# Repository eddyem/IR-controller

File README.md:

IR-controller
=============

Clone of same project from sourceforge

Don't use files from root directory, they are obsolete!!! 
Current code is in directory with_opencm3.

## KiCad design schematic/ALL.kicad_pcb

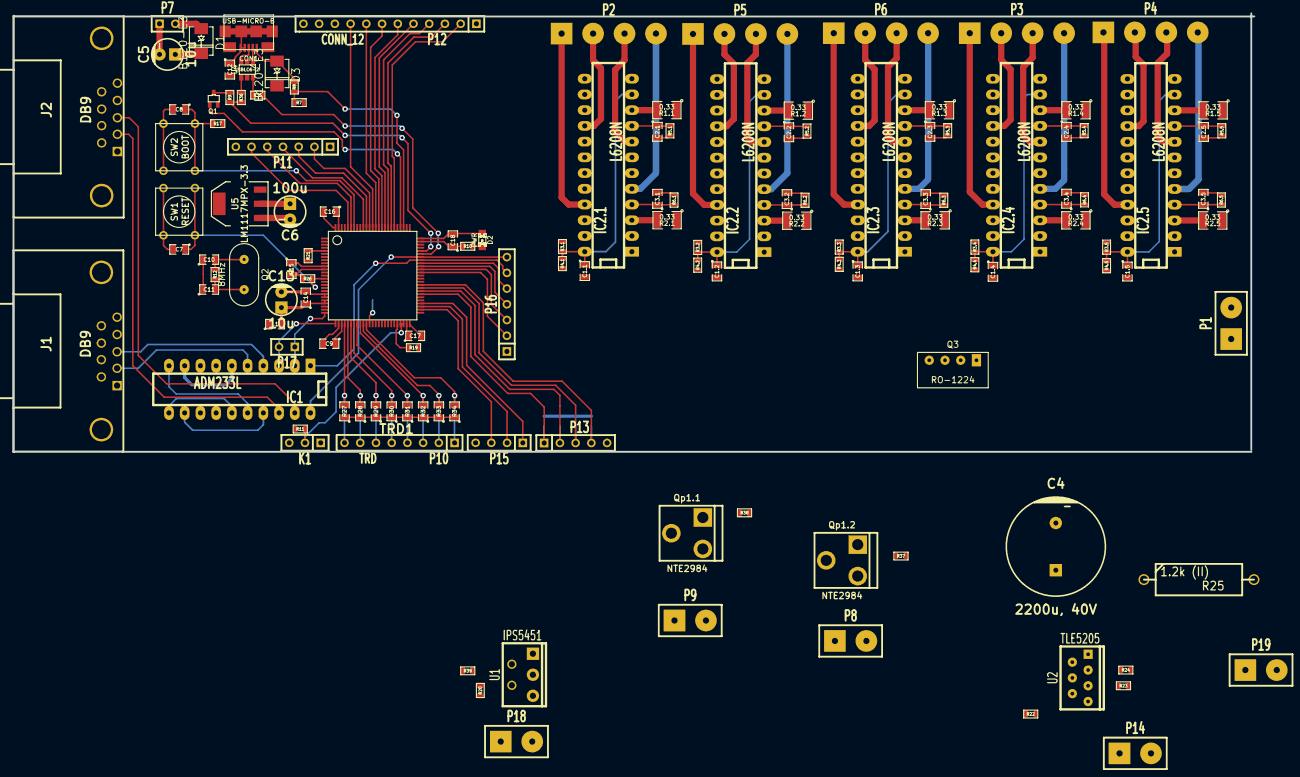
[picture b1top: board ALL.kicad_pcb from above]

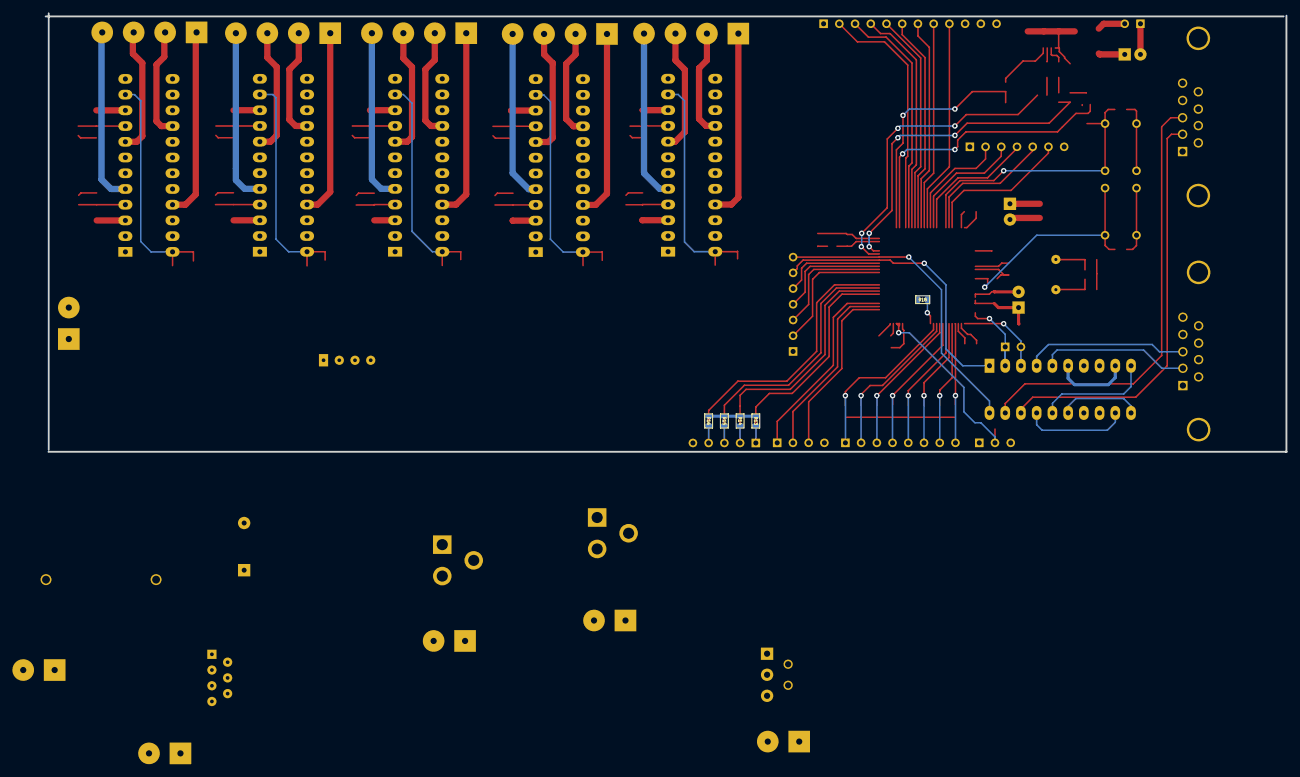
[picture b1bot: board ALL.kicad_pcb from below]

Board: 4 copper layers, 200.5 x 70.9 mm, 138 parts (5 on the bottom side), 142 nets.

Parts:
C1.1, C1.2, C1.3, C1.4, C1.5: 68n; SM0805
C2.1, C2.2, C2.3, C2.4, C2.5, C3.1, C3.2, C3.3, C3.4, C3.5: 1n; SM0805
C4: 2200u, 40V; CP_16x25mm
C5, C13: 10u; CP_5x11mm
C6: 100u; CP_5x11mm
C7, C8, C9, C12, C14, C15, C16, C17, C18: 100n; SM0805
C10, C11: 27p; SM0805
CON1: USB-MICRO-B; MICRO-B-USB
D1, D3: B120-E3; DO214
D2: PWR; LED-0805
IC1: ADM233L; DIP-20__300_ELL
IC2.1, IC2.2, IC2.3, IC2.4, IC2.5: L6208N; DIP-24__300_ELL
J1, J2: DB9; DB9FC
K1: CONN_3; SIL-3
L1: BMB2A0300AN1; SM0805
P1, P8, P9, P14, P18, P19: CONN_2; SIL-2-power
P2, P3, P4, P5, P6: CONN_4; SIL-4-power
P7, P17: CONN_2; SIL-2
P10: TRD; SIL-8
P11, P16: CONN_7; SIL-7
P12: CONN_12; SIL-12
P13: CONN_5; SIL-5
P15: CONN_4; SIL-4
Q1: DTA114Y; SOT323
Q2: 8MHz; hc49
Q3: RO-1224; SIP-4-RO
Qp1.1, Qp1.2: NTE2984; TO220-3-vert
R1.1, R1.2, R1.3, R1.4, R1.5, R2.1, R2.2, R2.3, R2.4, R2.5: 0.33; SM1210
R3.1, R3.2, R3.3, R3.4, R3.5, R7: 22k; SM0603
R4.1, R4.2, R4.3, R4.4, R4.5: 1.8k; SM0603
R5.1, R5.2, R5.3, R5.4, R5.5, R6.1, R6.2, R6.3, R6.4, R6.5: 51k; SM0603
R8, R20, R21: 15k; SM0603
R9: 1.5k; SM0603
R10: 510; SM0603
R11, R19: 4.7k; SM0603
R12: 1M; SM0603
R13, R14, R15, R16, R17, R22, R23, R24, R26, R37, R38, R39: 10k; SM0603
R18: 100k; SM0603
R25: 1.2k (II); R7
R27, R28, R29, R30, R31, R32, R33, R34: RT0805BRB071KL; SM0805
R35, R36: 22; SM0603
SW1: RESET; SW_PUSH_SMALL
SW2: BOOT; SW_PUSH_SMALL
U1: IPS5451; TO220-5
U2: TLE5205; TO220-7-12
U3: STM32F103; LQFP100_STM32
U4: USBLC6-2; SOT23_6
U5: LM1117MPX-3.3; SOT-223

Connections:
+3.3V: C6.1, C8.2, C9.1, C12.2, C15.2, C16.2, C17.2, C18.2, D2.1, L1.1, P11.7, Q1.2, R11.2, R20.2, R22.1, R23.1, R24.1, R26.2, SW2.1, U3.11, U3.28, U3.50, U3.75, U3.100, U4.5, U5.2
+5V: C5.1, D1.2, D3.2, IC1.7, IC2.1.13, IC2.1.23, IC2.2.13, IC2.2.23, IC2.3.13, IC2.3.23, IC2.4.13, IC2.4.23, IC2.5.13, IC2.5.23, K1.3, P12.1, R3.1.2, R3.2.2, R3.3.2, R3.4.2, R3.5.2, R13.2, R14.2, R15.2, R16.2, U5.3
/EP0: P13.1, R13.1, U3.57
/EP1: P13.2, R14.1, U3.58
/EP2: P13.3, R15.1, U3.59
/EP3: P13.4, R16.1, U3.60
/Filters slit #1/+10V: IC2.1.17, IC2.1.20, IC2.2.17, IC2.2.20, IC2.3.17, IC2.3.20, IC2.4.17, IC2.4.20, IC2.5.17, IC2.5.20, P1.2, P8.2, P9.2, Q3.1, U1.3
/Filters slit #1/+24V: IC2.1.15, IC2.2.15, IC2.3.15, IC2.4.15, IC2.5.15, Q3.3
/Filters slit #1/A: IC2.2.21, P5.1
/Filters slit #1/A*: IC2.2.16, P5.2
/Filters slit #1/B: IC2.2.5, P5.4
/Filters slit #1/B*: IC2.2.8, P5.3
/Filters slit #1/SM_CLK: IC2.1.1, IC2.2.1, IC2.3.1, U3.63
/Filters slit #1/SM_DIR: IC2.2.2, U3.98
/Filters slit #1/SM_EN: IC2.2.14, U3.39
/Filters slit #2/A: IC2.3.21, P6.1
/Filters slit #2/A*: IC2.3.16, P6.2
/Filters slit #2/B: IC2.3.5, P6.4
/Filters slit #2/B*: IC2.3.8, P6.3
/Filters slit #2/SM_DIR: IC2.3.2, U3.1
/Filters slit #2/SM_EN: IC2.3.14, U3.40
/Hall0: P12.2, U3.81
/Hall1: P12.3, U3.82
/Hall2: P12.4, U3.83
/Hall3: P12.5, U3.84
/Hall4: P12.6, U3.85
/Hall5: P12.7, U3.86
/Hall6: P12.8, U3.87
/Hall7: P12.9, U3.88
/Hall8: P12.10, U3.55
/Hall9: P12.11, U3.56
/Long stage/A: IC2.4.21, P3.1
/Long stage/A*: IC2.4.16, P3.2
/Long stage/B: IC2.4.5, P3.4
/Long stage/B*: IC2.4.8, P3.3
/Long stage/SM_CLK: IC2.4.1, IC2.5.1, U3.24
/Long stage/SM_DIR: IC2.4.2, U3.2
/Long stage/SM_EN: IC2.4.14, U3.41
/POW3: R19.2, R39.1, U3.46
/Power MOSFET module 1/GND_OUT: P8.1, Qp1.2.2
/Power MOSFET module 1/ON: Qp1.2.1, R37.1, U3.44
/Power MOSFET module 2/GND_OUT: P9.1, Qp1.1.2
/Power MOSFET module 2/ON: Qp1.1.1, R38.1, U3.45
/STM32F103 module/1-WIRE: K1.2, R11.1, U3.47, U3.48
/STM32F103 module/BOOT: C8.1, R17.1, SW2.2, U3.94
/STM32F103 module/DG_FEEDBACK: R21.1, U3.5
/STM32F103 module/EXT0: P16.2, U3.64
/STM32F103 module/EXT1: P16.3, U3.65
/STM32F103 module/EXT2: P16.4, U3.66
/STM32F103 module/EXT3: P16.5, U3.67
/STM32F103 module/I2C_SCL/CANRX: P11.5, U3.95
/STM32F103 module/I2C_SDA/CANTX: P11.6, U3.96
/STM32F103 module/RS-232 level converter/UART_RX: IC1.3, P17.2, U3.26
/STM32F103 module/RS-232 level converter/UART_RX1: IC1.20, P16.7, U3.69
/STM32F103 module/RS-232 level converter/UART_TX: IC1.2, P17.1, U3.25
/STM32F103 module/RS-232 level converter/UART_TX1: IC1.1, P16.6, U3.68
/STM32F103 module/RST: C7.1, R26.1, SW1.2, U3.14
/STM32F103 module/SHTR_FEEDBACK: R20.1, R21.2, U1.4
/STM32F103 module/SPI1_MISO: P11.3, U3.90
/STM32F103 module/SPI1_MOSI: P11.4, U3.91
/STM32F103 module/SPI1_SCK: P11.2, U3.89
/STM32F103 module/SPI2_MISO: P15.2, U3.53
/STM32F103 module/SPI2_MOSI: P15.1, U3.54
/STM32F103 module/SPI2_SCK: P15.3, U3.52
/STM32F103 module/USB input circuit/USB_DISC: Q1.1, U3.79
/STM32F103 module/USB input circuit/USB_DM: R35.2, U3.70
/STM32F103 module/USB input circuit/USB_DP: R9.2, R36.2, U3.71
/STM32F103 module/USB input circuit/USB_POWER: R7.1, R8.1, U3.78
/STM32F103 module/VDDA: C13.1, C14.1, L1.2, R27.1, R28.1, R29.1, R30.1, R31.1, R32.1, R33.1, R34.1, U3.21, U3.22
/Short stage/A: IC2.5.21, P4.1
/Short stage/A*: IC2.5.16, P4.2
/Short stage/B: IC2.5.5, P4.4
/Short stage/B*: IC2.5.8, P4.3
/Short stage/SM_DIR: IC2.5.2, U3.3
/Short stage/SM_EN: IC2.5.14, U3.42
/Shutter MOSFET/+36V: P19.2, R25.1
/Shutter MOSFET/EF: R22.2, U2.2, U3.16
/Shutter MOSFET/IN1: R24.2, U2.3, U3.43
/Shutter MOSFET/IN2: R23.2, U2.5, U3.15
/Shutter MOSFET/OUT1: P14.2, U2.1
/Shutter MOSFET/OUT2: P14.1, U2.7
/T1_0: P10.1, R34.2, U3.36
/T1_1: P10.2, R33.2, U3.35
/T1_2: P10.3, R32.2, U3.34
/T1_3: P10.4, R31.2, U3.33
/T1_4: P10.5, R30.2, U3.32
/T1_5: P10.6, R29.2, U3.31
/T1_6: P10.7, R28.2, U3.30
/T1_7: P10.8, R27.2, U3.29
/Turret slits/A: IC2.1.21, P2.1
/Turret slits/A*: IC2.1.16, P2.2
/Turret slits/B: IC2.1.5, P2.4
/Turret slits/B*: IC2.1.8, P2.3
/Turret slits/SM_DIR: IC2.1.2, U3.97
/Turret slits/SM_EN: IC2.1.14, U3.38
GND: C1.1.2, C1.2.2, C1.3.2, C1.4.2, C1.5.2, C2.1.2, C2.2.2, C2.3.2, C2.4.2, C2.5.2, C3.1.2, C3.2.2, C3.3.2, C3.4.2, C3.5.2, C4.2, C5.2, C6.2, C7.2, C9.2, C10.1, C11.1, C12.1, C13.2, C14.2, C15.1, C16.1, C17.1, C18.1, CON1.4, CON1.5, CON1.6, CON1.7, CON1.8, CON1.9, IC1.6, IC1.9, IC2.1.6, IC2.1.7, IC2.1.12, IC2.1.18, IC2.1.19, IC2.2.6, IC2.2.7, IC2.2.12, IC2.2.18, IC2.2.19, IC2.3.6, IC2.3.7, IC2.3.12, IC2.3.18, IC2.3.19, IC2.4.6, IC2.4.7, IC2.4.12, IC2.4.18, IC2.4.19, IC2.5.6, IC2.5.7, IC2.5.12, IC2.5.18, IC2.5.19, J1.5, J2.5, K1.1, P1.1, P7.1, P11.1, P12.12, P13.5, P15.4, P16.1, P18.1, P19.1, Q3.2, Q3.4, Qp1.1.3, Qp1.2.3, R1.1.1, R1.2.1, R1.3.1, R1.4.1, R1.5.1, R2.1.1, R2.2.1, R2.3.1, R2.4.1, R2.5.1, R4.1.2, R4.2.2, R4.3.2, R4.4.2, R4.5.2, R5.1.2, R5.2.2, R5.3.2, R5.4.2, R5.5.2, R6.1.2, R6.2.2, R6.3.2, R6.4.2, R6.5.2, R7.2, R10.1, R17.2, R18.2, R37.2, R38.2, R39.2, SW1.1, U1.1, U2.4, U3.10, U3.19, U3.20, U3.27, U3.49, U3.74, U3.99, U4.2, U5.1
unnamed: R19.1, U1.2
unnamed: P18.2, U1.5
unnamed: D1.1, P7.2
unnamed: C3.3.1, IC2.3.4, R6.3.1
unnamed: C2.3.1, IC2.3.9, R5.3.1
unnamed: IC2.3.3, R2.3.2
unnamed: IC2.3.10, R1.3.2
unnamed: C1.3.1, IC2.3.11, IC2.3.24, R3.3.1, R4.3.1
unnamed: R18.1, U3.37
unnamed: D2.2, R10.2
unnamed: C10.2, Q2.2, R12.1, U3.12
unnamed: C11.2, Q2.1, R12.2, U3.13
unnamed: C3.2.1, IC2.2.4, R6.2.1
unnamed: C2.2.1, IC2.2.9, R5.2.1
unnamed: IC2.2.3, R2.2.2
unnamed: IC2.2.10, R1.2.2
unnamed: C1.2.1, IC2.2.11, IC2.2.24, R3.2.1, R4.2.1
unnamed: C2.1.1, IC2.1.9, R5.1.1
unnamed: C1.1.1, IC2.1.11, IC2.1.24, R3.1.1, R4.1.1
unnamed: IC2.1.10, R1.1.2
unnamed: C3.1.1, IC2.1.4, R6.1.1
unnamed: IC2.1.3, R2.1.2
unnamed: IC2.5.10, R1.5.2
unnamed: C1.5.1, IC2.5.11, IC2.5.24, R3.5.1, R4.5.1
unnamed: C2.5.1, IC2.5.9, R5.5.1
unnamed: C3.5.1, IC2.5.4, R6.5.1
unnamed: IC2.5.3, R2.5.2
unnamed: IC2.4.3, R2.4.2
unnamed: IC2.4.10, R1.4.2
unnamed: C2.4.1, IC2.4.9, R5.4.1
unnamed: C3.4.1, IC2.4.4, R6.4.1
unnamed: C1.4.1, IC2.4.11, IC2.4.24, R3.4.1, R4.4.1
unnamed: C4.1, R25.2, U2.6
unnamed: IC1.5, J1.2
unnamed: IC1.4, J1.3
unnamed: IC1.12, IC1.17
unnamed: IC1.11, IC1.15
unnamed: IC1.10, IC1.16
unnamed: IC1.18, J2.2
unnamed: IC1.19, J2.3
unnamed: Q1.3, R9.1
unnamed: R36.1, U4.4
unnamed: R35.1, U4.6
unnamed: CON1.2, U4.1
unnamed: CON1.3, U4.3
unnamed: CON1.1, D3.1, R8.2

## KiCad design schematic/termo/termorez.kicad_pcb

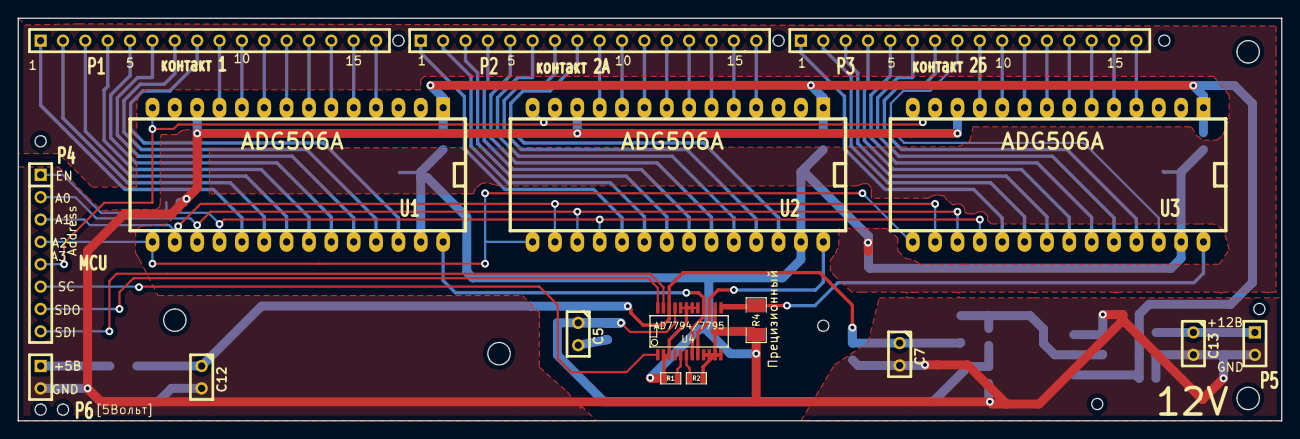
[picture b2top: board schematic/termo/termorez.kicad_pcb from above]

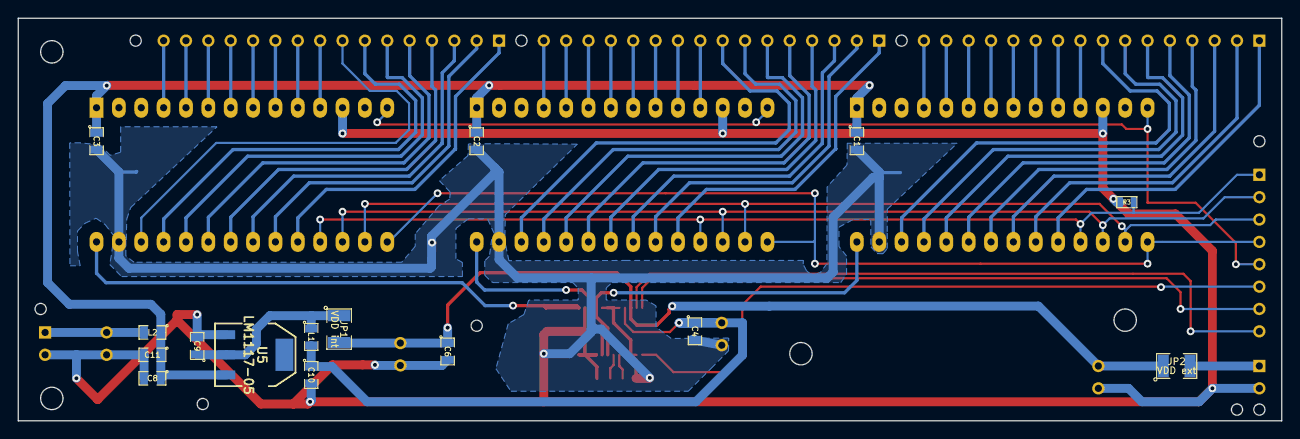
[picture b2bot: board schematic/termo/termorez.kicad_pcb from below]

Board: 2 copper layers, 143.5 x 45.7 mm, 32 parts (15 on the bottom side), 68 nets.

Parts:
C1, C2, C3, C4, C6, C9: 0.1u; SM0805
C5, C7, C12: 10u; C1
C8: 0.33u; SM0805
C10, C11: 1u; SM0805
C13: 100u; C1
JP1: VDD int; SM1210
JP2: VDD ext; SM1210
L1, L2: BMB2A0300AN1; SM0805
P1: контакт 1; SIL-16
P2: контакт 2А; SIL-16
P3: контакт 2Б; SIL-16
P4: MCU; SIL-8
P5: 12V; SIL-2
P6: 5Вольт; SIL-2
R1, R2: 10k; SM0603
R3: 47k; SM0603
R4: 5.1k PREC!; SM1206
U1, U2, U3: ADG506A; DIP-28__600_ELL
U4: AD7794/7795; SSOP24
U5: LM1117-05; SOT223

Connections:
+5VA: C4.1, C5.1, C10.1, L1.2, U4.21
+12V: C1.1, C2.1, C3.1, C8.1, C11.1, L2.1, U1.1, U2.1, U3.1, U5.3
+12Vex: C13.1, L2.2, P5.1
/A0: P4.2, U1.17, U2.17, U3.17
/A1: P4.3, U1.16, U2.16, U3.16
/A2: P4.4, U1.15, U2.15, U3.15
/A3: P4.5, U1.14, U2.14, U3.14
/EN: P4.1, R3.1, U1.18, U2.18, U3.18
/SC: P4.6, U4.1
/SDI: P4.8, U4.23
/SDO: P4.7, U4.24
DVDD: JP2.2, P6.1
GND: C1.2, C2.2, C3.2, C4.2, C5.2, C6.2, C7.2, C8.2, C9.2, C10.2, C11.2, C12.2, C13.2, P5.2, P6.2, R1.2, R2.2, R3.2, R4.2, U1.12, U1.27, U2.12, U2.27, U3.12, U3.27, U4.2, U4.3, U4.9, U4.10, U4.11, U4.12, U4.14, U4.17, U4.18, U4.19, U4.20, U5.1
unnamed: P1.3, U1.21
unnamed: P1.2, U1.20
unnamed: P1.1, U1.19
unnamed: P1.16, U1.4
unnamed: P1.15, U1.5
unnamed: P1.14, U1.6
unnamed: P1.13, U1.7
unnamed: P1.12, U1.8
unnamed: P1.11, U1.9
unnamed: P1.10, U1.10
unnamed: P1.9, U1.11
unnamed: P1.8, U1.26
unnamed: P1.7, U1.25
unnamed: P1.6, U1.24
unnamed: P1.5, U1.23
unnamed: P1.4, U1.22
unnamed: R2.1, U4.6
unnamed: P2.3, U2.21
unnamed: P2.2, U2.20
unnamed: P2.1, U2.19
unnamed: P2.16, U2.4
unnamed: P2.15, U2.5
unnamed: P2.14, U2.6
unnamed: P2.13, U2.7
unnamed: P2.12, U2.8
unnamed: P2.11, U2.9
unnamed: P2.10, U2.10
unnamed: P2.9, U2.11
unnamed: P2.8, U2.26
unnamed: P2.7, U2.25
unnamed: P2.6, U2.24
unnamed: P2.5, U2.23
unnamed: P2.4, U2.22
unnamed: R1.1, U4.5
unnamed: R4.1, U3.28, U4.13
unnamed: U1.28, U4.7, U4.16
unnamed: U2.28, U4.8, U4.15
unnamed: C9.1, JP1.1, L1.1, U5.2
unnamed: P3.3, U3.21
unnamed: P3.2, U3.20
unnamed: P3.1, U3.19
unnamed: P3.16, U3.4
unnamed: P3.15, U3.5
unnamed: P3.14, U3.6
unnamed: P3.13, U3.7
unnamed: P3.12, U3.8
unnamed: P3.11, U3.9
unnamed: P3.10, U3.10
unnamed: P3.9, U3.11
unnamed: P3.8, U3.26
unnamed: P3.7, U3.25
unnamed: P3.6, U3.24
unnamed: P3.5, U3.23
unnamed: P3.4, U3.22
VDD: C6.1, C7.1, C12.1, JP1.2, JP2.1, U4.22

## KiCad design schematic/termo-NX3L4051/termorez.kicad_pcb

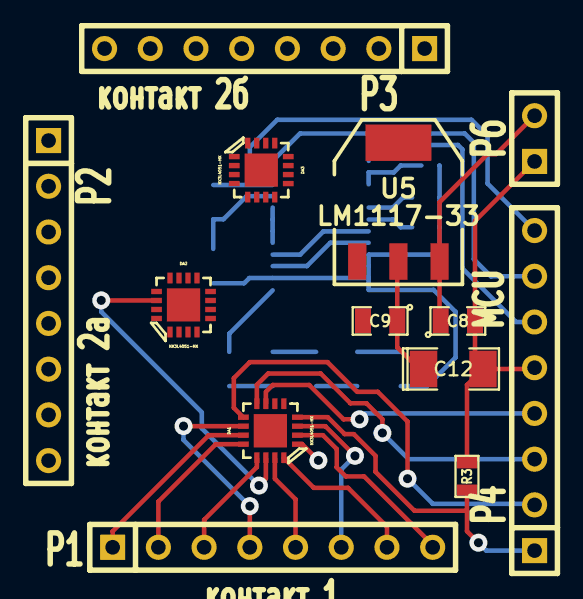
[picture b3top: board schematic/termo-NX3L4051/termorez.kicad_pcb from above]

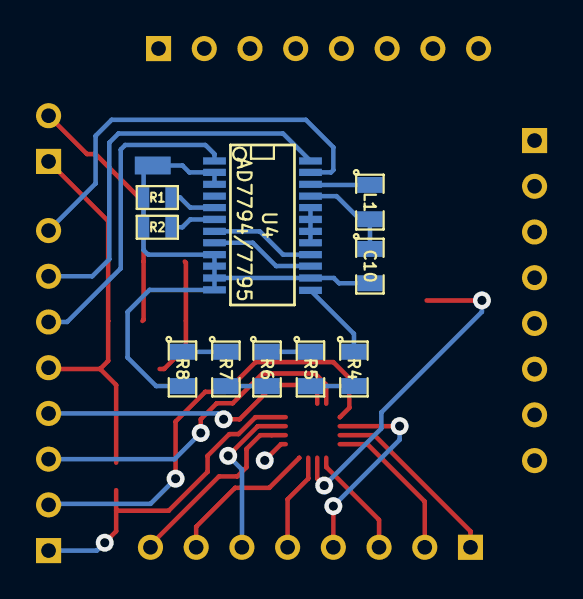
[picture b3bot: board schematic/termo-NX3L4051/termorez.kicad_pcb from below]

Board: 2 copper layers, 24 parts (11 on the bottom side), 45 nets.

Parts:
C8: 0.33u; SM0805
C9: 0.1u; SM0805
C10: 1u; SM0805
C12: 47u; SM1206POL
DA1, DA2, DA3: NX3L4051-HX; HXQFN16
L1: BMB2A0300AN1; SM0805
P1: контакт 1; SIL-8
P2: контакт 2a; SIL-8
P3: контакт 2б; SIL-8
P4: MCU; SIL-8
P6: 5V; SIL-2
R1, R2: 10k; SM0603
R3: 47k; SM0603
R4, R5, R6, R7, R8: 1k 0.1% (RT0805BRB071KL); SM0805
U4: AD7794/7795; SSOP24
U5: LM1117-33; SOT223
X1: GND_CONNECTOR; GND_connector

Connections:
+3.3V: C10.1, L1.2, U4.21
/A0: DA1.9, DA2.9, DA3.9, P4.2
/A1: DA1.8, DA2.8, DA3.8, P4.3
/A2: DA1.7, DA2.7, DA3.7, P4.4
/EN: DA1.4, DA2.4, DA3.4, P4.1, R3.1
/SC: P4.6, U4.1
/SDI: P4.8, U4.23
/SDO: P4.7, U4.24
AGND: C10.2, DA1.6, DA2.6, DA3.6, R1.2, R2.2, R8.2, U4.9, U4.10, U4.11, U4.12, U4.14, U4.17, U4.18, U4.19, U4.20, X1.2
DVDD: C8.1, P6.2, U5.3
GND: C8.2, C9.2, C12.2, P4.5, P6.1, R3.2, U4.2, U4.3, U5.1, X1.1
unnamed: DA1.1, U4.7, U4.16
unnamed: DA3.16, P3.7
unnamed: DA3.3, P3.6
unnamed: DA3.2, P3.8
unnamed: DA1.16, P1.7
unnamed: DA1.15, P1.5
unnamed: DA1.13, P1.3
unnamed: DA2.3, P2.6
unnamed: DA2.13, P2.3
unnamed: DA2.12, P2.2
unnamed: DA2.11, P2.1
unnamed: DA2.10, P2.4
unnamed: DA1.12, P1.2
unnamed: DA2.2, P2.8
unnamed: DA3.10, P3.4
unnamed: DA3.13, P3.3
unnamed: DA3.12, P3.2
unnamed: DA3.11, P3.1
unnamed: DA2.16, P2.7
unnamed: DA2.15, P2.5
unnamed: DA3.15, P3.5
unnamed: DA1.11, P1.1
unnamed: DA1.10, P1.4
unnamed: DA1.3, P1.6
unnamed: DA1.2, P1.8
unnamed: R4.2, R5.2
unnamed: R6.2, R7.2
unnamed: R5.1, R6.1
unnamed: R7.1, R8.1
unnamed: DA3.1, R4.1, U4.13
unnamed: DA2.1, U4.8, U4.15
unnamed: R2.1, U4.6
unnamed: R1.1, U4.5
VDD: C9.1, C12.1, DA1.14, DA2.14, DA3.14, L1.1, U4.22, U5.2

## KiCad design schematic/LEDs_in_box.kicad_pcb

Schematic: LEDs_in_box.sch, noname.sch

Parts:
D1, D2, D3, D4, D5: LED
HOLE1, HOLE2, HOLE3, HOLE4: HOLE
K1: CONN_3
K2: CONN_4
R1, R2: 330; SM0603
R3, R4: 2.2k; SM0603
R5: 6.8k; SM1206

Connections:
unnamed: D3.1 (A), K2.1
unnamed: D4.1 (A), K2.3
unnamed: D5.2 (K), R5.2
unnamed: K2.4, R3.1, R4.1, R5.1
unnamed: D4.2 (K), R4.2
unnamed: D3.2 (K), R3.2
unnamed: D5.1 (A), K2.2
unnamed: D1.1 (A), R1.2
unnamed: D1.2 (K), K1.1
unnamed: D2.2 (K), K1.2 (PM)
unnamed: K1.3, R1.1, R2.1
unnamed: D2.1 (A), R2.2

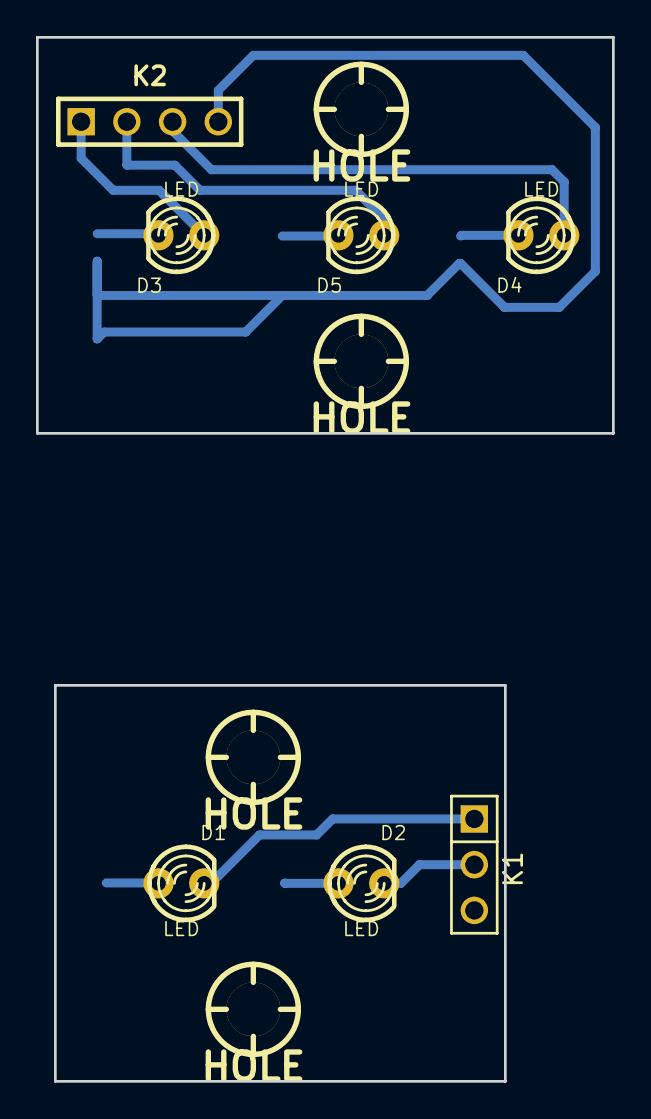
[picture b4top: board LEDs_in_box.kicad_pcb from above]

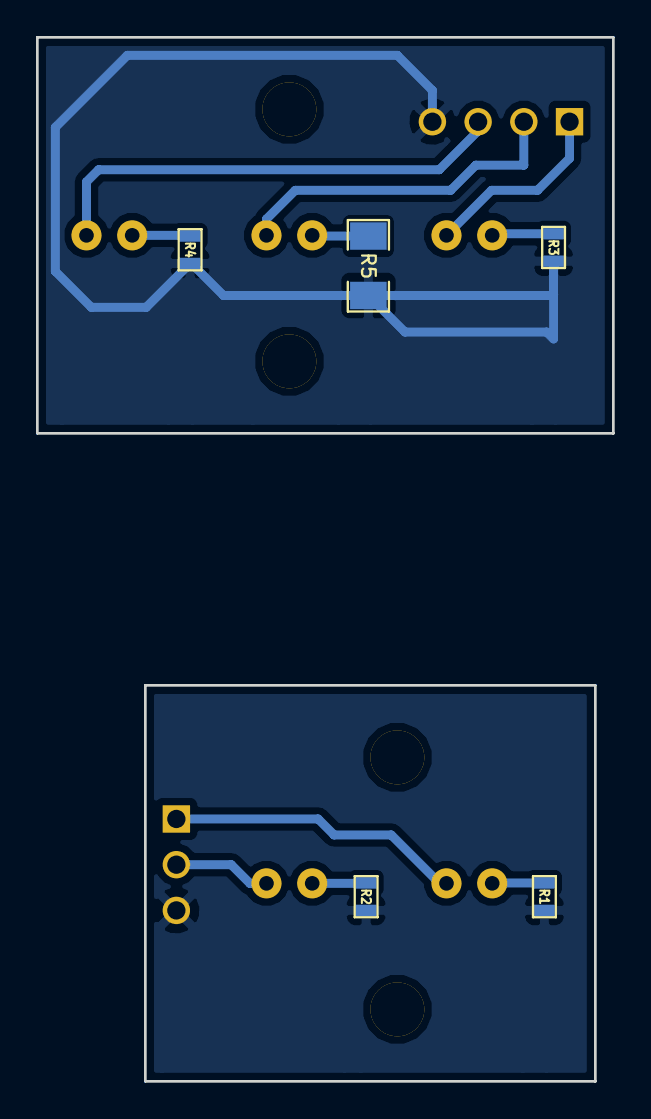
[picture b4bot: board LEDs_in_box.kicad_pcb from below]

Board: 2 copper layers, 32.0 x 58.0 mm, 16 parts (5 on the bottom side), 12 nets.

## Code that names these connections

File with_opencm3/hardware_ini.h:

/*
 * hardware_ini.h
 *
 * Copyright 2014 Edward V. Emelianov <eddy@sao.ru, edward.emelianoff@gmail.com>
 *
 * This program is free software; you can redistribute it and/or modify
 * it under the terms of the GNU General Public License as published by
 * the Free Software Foundation; either version 2 of the License, or
 * (at your option) any later version.
 *
 * This program is distributed in the hope that it will be useful,
 * but WITHOUT ANY WARRANTY; without even the implied warranty of
 * MERCHANTABILITY or FITNESS FOR A PARTICULAR PURPOSE.  See the
 * GNU General Public License for more details.
 *
 * You should have received a copy of the GNU General Public License
 * along with this program; if not, write to the Free Software
 * Foundation, Inc., 51 Franklin Street, Fifth Floor, Boston,
 * MA 02110-1301, USA.
 */

#pragma once
#ifndef __HARDWARE_INI_H__
#define __HARDWARE_INI_H__


// to have a compatibility with medium-density devices we can use only timers 1..4!!!
/*
 * Timers:
 * SysTick - system time
 * TIM1 - not used
 * TIM2 - 1-wire
 * TIM3, TIM4 - stepper motors
 */


extern volatile uint16_t ADC_value[]; // ADC DMA value

#define TRD_NO			(8) // number of TRD devices
// bits used to address external SPI ADC - PD10..12
#define ADC_ADDR_MASK	(GPIO10|GPIO11|GPIO12)
#define ADC_SET_ADDR(X)	((X << 10) & ADC_ADDR_MASK)
#define ADC_EN_PIN		GPIO13
#define ADC_ADDR_PORT	GPIOD

void SPI1_init();
void SPI2_init();
void GPIO_init();
void SysTick_init();
void ADC_init();
void ADC_calibrate_and_start();

void adc_dma_on();

/*
 * USB interface
 */
// USB_DICS (disconnect) - PC11
#define USB_DISC_PIN		GPIO11
#define USB_DISC_PORT		GPIOC
// USB_POWER (high level when USB connected to PC)
#define USB_POWER_PIN		GPIO10
#define USB_POWER_PORT		GPIOC
// change signal level on USB diconnect pin
#define usb_disc_high()   gpio_set(USB_DISC_PORT, USB_DISC_PIN)
#define usb_disc_low()    gpio_clear(USB_DISC_PORT, USB_DISC_PIN)
// in case of n-channel FET on 1.5k pull-up change on/off disconnect means low level
// in case of pnp bipolar transistor or p-channel FET on 1.5k pull-up disconnect means high level
#define usb_disconnect()  usb_disc_high()
#define usb_connect()     usb_disc_low()

/*
 * Stepper motors
 * motors' interface use timers 1 & 2, so even hardware-dependent functions are
 * 		moved to stepper_motors.c
 */
// PE7..11 - EN
#define MOTOR_EN_MASK		(0x1f << 7)
#define MOTOR_EN_PORT		(GPIOE)
// N == 0..4
#define MOTOR_EN_PIN(N)		(GPIO7 << (N))
// PE0..PE5 - DIR
#define MOTOR_DIR_MASK		(0x1f)
#define MOTOR_DIR_PORT		(GPIOE)
// N == 0..4
#define MOTOR_DIR_PIN(N)	(GPIO0 << (N))
// timers: TIM1 - PC6, TIM2 - PD15
#define MOTOR_TIM1_PORT		(GPIOC)
#define MOTOR_TIM1_PIN		(GPIO6)
#define MOTOR_TIM2_PORT		(GPIOD)
#define MOTOR_TIM2_PIN		(GPIO15)
// don't even try to move motor if motors' voltage less than 9.0V
#define MOTORS_VOLTAGE_THRES  (900)
// stop all motors if voltage less than 7.5V
#define MOTORS_VOLTAGE_ALERT  (750)

/*
 * One Wire interface
 *
// In case of using other USART for 1-wire port, make corresponding change
// and redefine pins in OW_Init
#define OW_USART_X			USART2
#define OW_RX_PORT			GPIO_BANK_USART2_RX
#define OW_RX_PIN			GPIO_USART2_RX
*/
/*
 * Shutter defines
 */
// external signals for shutter opening: PB3 (SPI1_SCK) - from camera electronics, PB4 (SPI1_MISO) - from manual switch
// both are pull-up inputs
//#define SHUTTER_CAM_PORT	(GPIOB)
//#define SHUTTER_CAM_PIN		(GPIO3)
// As PB3 was burned, redefine CAM to EXT0 - PD10
#define SHUTTER_CAM_PORT	(GPIOD)
#define SHUTTER_CAM_PIN		(GPIO10)
#define SHUTTER_MAN_PORT	(GPIOB)
#define SHUTTER_MAN_PIN		(GPIO4)
// shutter feedback ==0 when opened, PB5 (SPI1_MOSI)
#define SHUTTER_FBSW_PORT	(GPIOB)
#define SHUTTER_FBSW_PIN	(GPIO5)
// LED status open-drain output: PB8 (CAN RX)
#define LED_STATUS_PORT		(GPIOB)
#define LED_STATUS_PIN		(GPIO8)
#define LED_STATUS_OK()		do{gpio_clear(LED_STATUS_PORT, LED_STATUS_PIN);}while(0)
#define LED_STATUS_BAD()	do{gpio_set(LED_STATUS_PORT, LED_STATUS_PIN);}while(0)
// Shutter LED (lights when shutter opened) open-drain output, PB9 (CAN TX)
#define LED_SHUTTER_PORT	(GPIOB)
#define LED_SHUTTER_PIN		(GPIO9)
#define LED_SHUTTER_OPEN()	do{gpio_clear(LED_SHUTTER_PORT, LED_SHUTTER_PIN);}while(0)
#define LED_SHUTTER_CLOSE()	do{gpio_set(LED_SHUTTER_PORT, LED_SHUTTER_PIN);}while(0)

// Shutter pins: PC0 & PC2 are polarity & on/off pins; PC1 is feedback pin
#define SHUTTER_PORT           (GPIOC)
#define SHUTTER_ON_PIN         (GPIO2)
#define SHUTTER_POLARITY_PIN   (GPIO0)
#define SHUTTER_FB_PIN         (GPIO1)
// voltage (*100) threshold to run shutter - 20V
#define SHUTTER_VOLTAGE_THRES  (2000)
// minimum voltage that should be on capasitor if power source is on
#define SHUTTER_UNDERVOLTAGE_THRES  (700)
// delay in operations (open/close) in milliseconds (according to shutter's datasheet it's about 12ms -> make 15)
#define SHUTTER_DELAY  (15)
// delay for error test (in microseconds)
#define SHUTTER_OP_DELAY (200)

// ADC_value[8] is U36, ADC_value[9] is U10
#define SHUTTER_SENSE_NUMBER  (8)
#define POWER_SENSE_NUMBER    (9)
int shutter_voltage();
int power_voltage();
int TRD_value(uint8_t num);

#endif // __HARDWARE_INI_H__

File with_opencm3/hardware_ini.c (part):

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	rcc_peripheral_enable_clock(&RCC_APB2ENR, RCC_APB2ENR_AFIOEN | RCC_APB2ENR_IOPBEN);
	// SCK, MOSI - push-pull output
	gpio_set_mode(GPIO_BANK_SPI2_SCK, GPIO_MODE_OUTPUT_50_MHZ,
		GPIO_CNF_OUTPUT_ALTFN_PUSHPULL, GPIO_SPI2_SCK);
	gpio_set_mode(GPIO_BANK_SPI2_MOSI, GPIO_MODE_OUTPUT_50_MHZ,
		GPIO_CNF_OUTPUT_ALTFN_PUSHPULL, GPIO_SPI2_MOSI);
	// MISO - opendrain in
	gpio_set_mode(GPIO_BANK_SPI2_MISO, GPIO_MODE_INPUT, GPIO_CNF_INPUT_FLOAT, GPIO_SPI2_MISO);
	spi_reset(SPI2);
	/* Set up SPI in Master mode with:
	 * Clock baud rate: 1/64 of peripheral clock frequency (APB1, 36MHz)
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			RCC_APB2ENR_IOPBEN | RCC_APB2ENR_IOPCEN | RCC_APB2ENR_IOPDEN |
			RCC_APB2ENR_IOPEEN);
	// USB_DISC: push-pull
	gpio_set_mode(USB_DISC_PORT, GPIO_MODE_OUTPUT_2_MHZ,
				GPIO_CNF_OUTPUT_PUSHPULL, USB_DISC_PIN);
	// USB_POWER: open drain, externall pull down with R7 (22k)
	gpio_set_mode(USB_POWER_PORT, GPIO_MODE_INPUT,
				GPIO_CNF_INPUT_FLOAT, USB_POWER_PIN);
	// AD7794 addr + en
	gpio_set_mode(ADC_ADDR_PORT, GPIO_MODE_OUTPUT_2_MHZ,
				GPIO_CNF_OUTPUT_PUSHPULL, ADC_ADDR_MASK | ADC_EN_PIN); // ADDRESS: PD10..12; EN: PD13
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
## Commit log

2014-03-18 copy
2014-07-09 added schematic
2014-07-14 gitignore
2014-07-17 plugs
2014-07-18 last?
2014-07-21 Buttons
2014-07-22 Initial run for realisation with opencm3 library
2014-07-23 Added USART support (Up to three USARTs)
2014-07-24 Added one channel ADC through DMA
2014-08-13 Code review + scan ability for TRDs
2014-08-14 Added some statistics about measured data
2014-09-23 modified client.c
2014-09-23 fixed bug with USB buffer lost
2014-09-29 1st try to fix errors on PCB
2014-10-30 try to make 1-wire on timers
2014-12-02 modified schematics
2015-01-26 commit before large work
2015-01-27 Add something to stepper_motors.c + make little modifications
2015-02-03 some modifications, shutter not work :(
2015-02-04 Shutter module tested
2015-02-05 added flash support
2015-02-06 fixed errors in flash write module
2015-03-24 Added string protocol + some modifications of code
2015-04-17 A lot of errors fixed
2015-04-22 Steppers worked & tested; inner ADC works fine; add median filtering by 9 points for TRD resistance values
2015-04-22 make some cleanup
2015-04-24 Added some documentation
2015-05-14 Fixed bugs when work in mustdie's terminal
2015-07-28 added 1-wire support
2015-07-28 Modified documentation
2015-08-04 add init on poweron
2015-08-04 documentation
2016-04-21 fix error in 1-wire data conversion for DS18B20
2023-08-08 save under new kicad
